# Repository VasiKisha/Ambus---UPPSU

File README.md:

# Ambus---UPPSU

View this project on [CADLAB.io](https://cadlab.io/project/24060). 

## Ambus Commands
|Command   |Description                          |
|:--------:|:-----------------------------------:|
| DEV?     | get device description              |
| FW?      | get firmware version                |
| SWITCH?  | get HW switch state                 |
| MODE?    | get CC/CV mode                      |
| VOLT?    | get measured output volrage         |
| CURR?    | get measured output current         |
| SETV(?)  | set(get) output voltage             |
| SETC(?)  | set(get) output current             |
| SWREM(?) | set(get) remote output control      |
| OUTPUT?  | get output relay state              |
| CALVG(?) | set(get) calibration voltage gain   |
| CALVO(?) | set(get) calibration voltage offset |
| CALIG(?) | set(get) calibration current gain   |
| CALIO(?) | set(get) calibration current offset |
| SAVE     | save settings to EEPROM             |
| LOAD     | load settings from EEPROM           |

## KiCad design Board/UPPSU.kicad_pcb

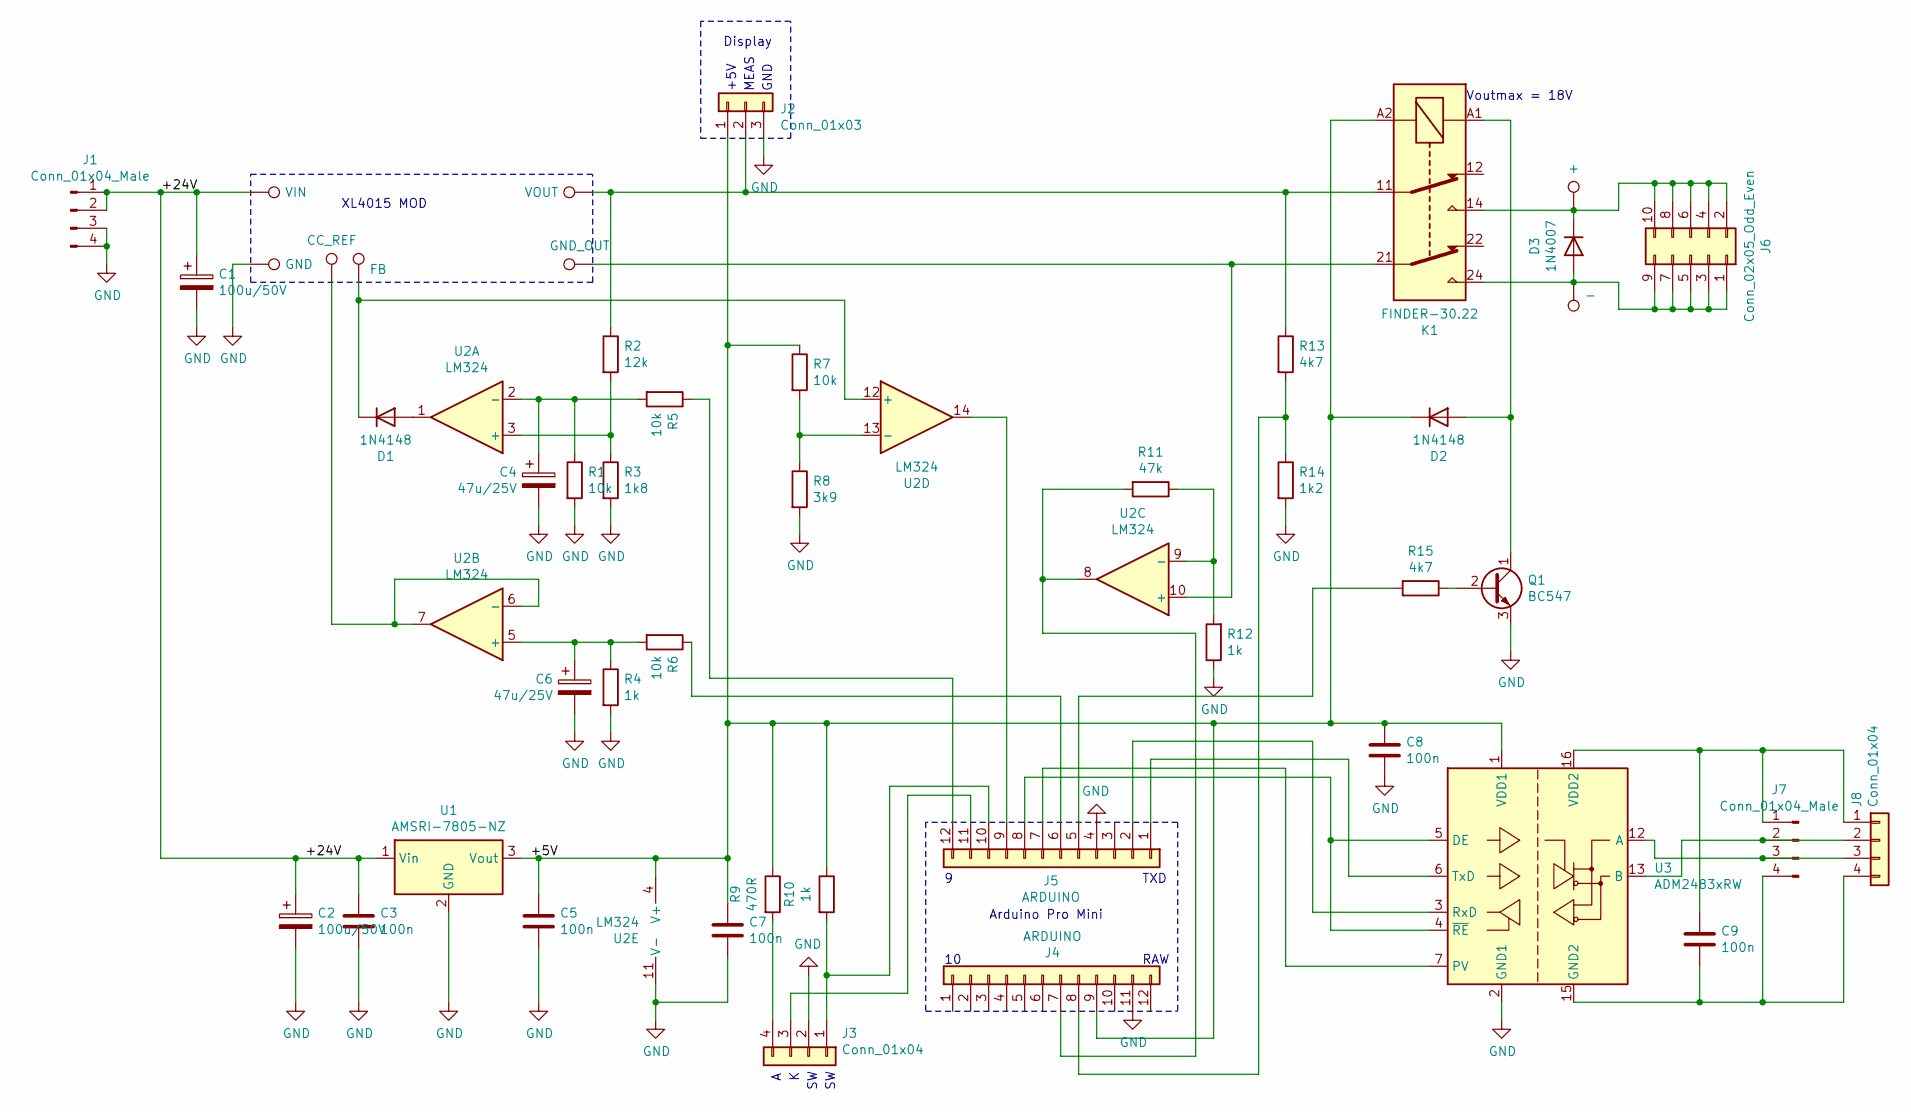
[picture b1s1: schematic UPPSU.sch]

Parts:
C1, C2: 100u/50V; CP_Radial_D16.0mm_P7.50mm
C3, C5, C7, C8, C9: 100n; C_Disc_D4.3mm_W1.9mm_P5.00mm
C4, C6: 47u/25V; CP_Radial_D5.0mm_P2.00mm
D1, D2: 1N4148; D_DO-35_SOD27_P7.62mm_Horizontal
D3: 1N4007; D_DO-35_SOD27_P7.62mm_Horizontal
J1, J7: Conn_01x04_Male; PhoenixContact_MSTBVA_2,5_4-G-5,08_1x04_P5.08mm_Vertical
J2: Conn_01x03; PinHeader_1x03_P2.54mm_Vertical
J3, J8: Conn_01x04; PinHeader_1x04_P2.54mm_Vertical
J4, J5: ARDUINO; PinSocket_1x12_P2.54mm_Vertical
J6: Conn_02x05_Odd_Even; PinSocket_2x05_P2.54mm_Horizontal
K1: FINDER-30.22; Relay_DPDT_Finder_30.22
Q1: BC547; TO-92_Inline
R1, R5, R6, R7: 10k; R_Axial_DIN0207_L6.3mm_D2.5mm_P7.62mm_Horizontal
R2: 12k; R_Axial_DIN0207_L6.3mm_D2.5mm_P7.62mm_Horizontal
R3: 1k8; R_Axial_DIN0207_L6.3mm_D2.5mm_P7.62mm_Horizontal
R4, R10, R12: 1k; R_Axial_DIN0207_L6.3mm_D2.5mm_P7.62mm_Horizontal
R8: 3k9; R_Axial_DIN0207_L6.3mm_D2.5mm_P7.62mm_Horizontal
R9: 470R; R_Axial_DIN0207_L6.3mm_D2.5mm_P7.62mm_Horizontal
R11: 47k; R_Axial_DIN0207_L6.3mm_D2.5mm_P7.62mm_Horizontal
R13, R15: 4k7; R_Axial_DIN0207_L6.3mm_D2.5mm_P7.62mm_Horizontal
R14: 1k2; R_Axial_DIN0207_L6.3mm_D2.5mm_P7.62mm_Horizontal
TP1: VIN; SolderWire-2.5sqmm_1x01_D2.4mm_OD4.4mm
TP2: GND; SolderWire-2.5sqmm_1x01_D2.4mm_OD4.4mm
TP3: CC_REF; SolderWire-0.25sqmm_1x01_D0.65mm_OD2mm
TP4: FB; SolderWire-0.25sqmm_1x01_D0.65mm_OD2mm
TP5: VOUT; SolderWire-2.5sqmm_1x01_D2.4mm_OD4.4mm
TP6: GND_OUT; SolderWire-2.5sqmm_1x01_D2.4mm_OD4.4mm
TP7: +; SolderWire-2.5sqmm_1x01_D2.4mm_OD4.4mm
TP8: -; SolderWire-2.5sqmm_1x01_D2.4mm_OD4.4mm
U1: AMSRI-7805-NZ; Converter_DCDC_TRACO_TSR-1_THT
U2: LM324; DIP-14_W7.62mm
U3: ADM2483xRW; SOIC-16W_7.5x10.3mm_P1.27mm

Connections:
/+5V: C5.1, C7.1, C8.1, D2.1 (K), J2.1, J4.9, K1.A2, R7.1, R9.1, R10.1, U1.3 (Vout), U2.4 (V+), U3.1 (VDD1)
/+24V: C1.1, C2.1, C3.1, J1.1, J1.2, TP1.1, U1.1 (Vin)
GND: C1.2, C2.2, C3.2, C4.2, C5.2, C6.2, C7.2, C8.2, J1.3, J1.4, J2.3, J3.2, J4.11, J5.4, Q1.3 (E), R1.2, R3.2, R4.2, R8.2, R12.1, R14.2, TP2.1, U1.2 (GND), U2.11 (V-), U3.2 (GND1), U3.8 (GND1)
unnamed: C4.1, R1.1, R5.2, U2.2 (-)
unnamed: C6.1, R4.1, R6.2, U2.5 (+)
unnamed: C9.1, J7.1, J8.1, U3.16 (VDD2)
unnamed: C9.2, J7.4, J8.4, U3.9 (GND2), U3.15 (GND2)
unnamed: D1.1 (K), TP4.1, U2.12 (+)
unnamed: D1.2 (A), U2.1
unnamed: D2.2 (A), K1.A1, Q1.1 (C)
unnamed: D3.1 (K), J6.2, J6.4, J6.6, J6.8, J6.10, K1.14, TP7.1
unnamed: D3.2 (A), J6.1, J6.3, J6.5, J6.7, J6.9, K1.24, TP8.1
unnamed: J2.2, K1.11, R2.1, R13.1, TP5.1
unnamed: J3.1, J5.10, R10.2
unnamed: J3.3, J5.11
unnamed: J3.4, R9.2
unnamed: J4.7, R11.2, U2.8
unnamed: J4.8, R13.2, R14.1
unnamed: J5.1, U3.6 (TxD)
unnamed: J5.2, U3.3 (RxD)
unnamed: J5.5, R15.2
unnamed: J5.6, R6.1
unnamed: J5.7, U3.7 (PV)
unnamed: J5.8, U3.4 (~RE), U3.5 (DE)
unnamed: J5.9, U2.14
unnamed: J5.12, R5.1
unnamed: J7.2, J8.2, U3.13 (B)
unnamed: J7.3, J8.3, U3.12 (A)
unnamed: K1.21, TP6.1, U2.10 (+)
unnamed: Q1.2 (B), R15.1
unnamed: R2.2, R3.1, U2.3 (+)
unnamed: R7.2, R8.1, U2.13 (-)
unnamed: R11.1, R12.2, U2.9 (-)
unnamed: TP3.1, U2.6 (-), U2.7

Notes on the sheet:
XL4015 MOD
Arduino Pro Mini
Display
Voutmax = 18V
RAW
TXD
+5V
MEAS
GND

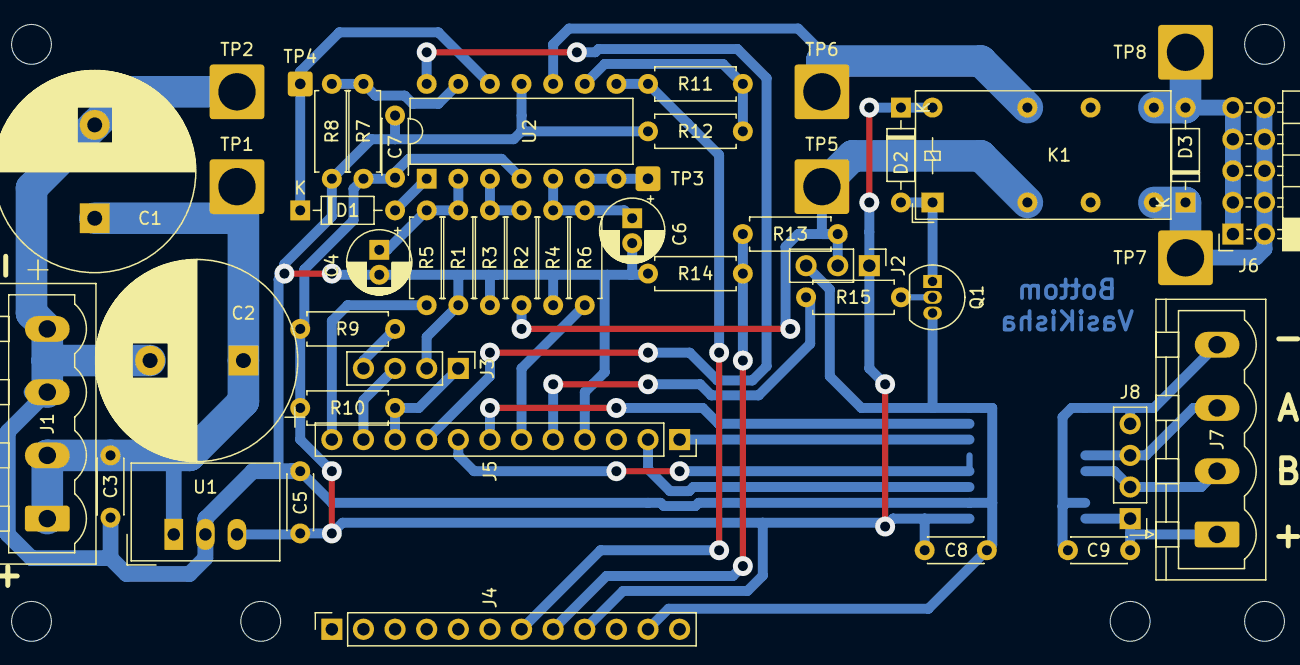
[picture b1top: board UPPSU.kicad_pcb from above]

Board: 2 copper layers, 48 parts (1 on the bottom side), 34 nets.

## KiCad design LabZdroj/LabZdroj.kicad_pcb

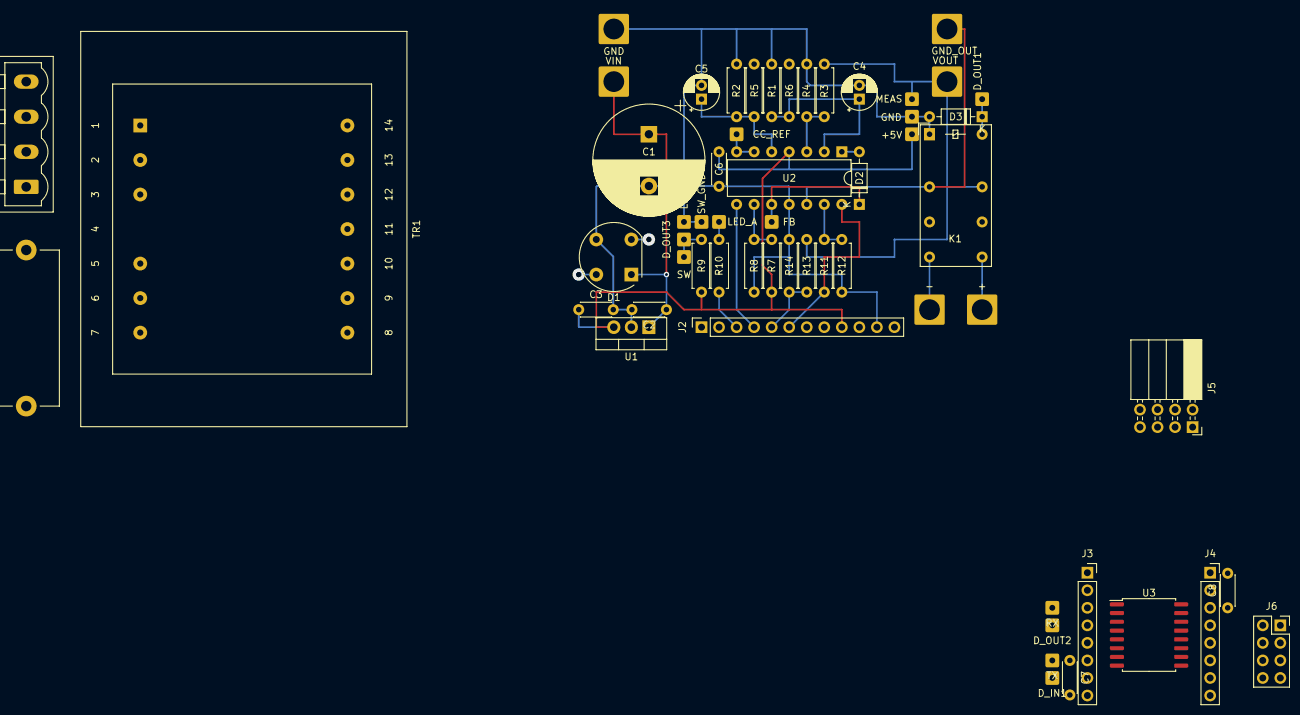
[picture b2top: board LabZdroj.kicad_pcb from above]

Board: 2 copper layers, 58 parts (0 on the bottom side), 37 nets.

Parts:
C1: 2200u/35V; CP_Radial_D16.0mm_P7.50mm
C2, C3, C6, C7, C8: 100n; C_Disc_D4.3mm_W1.9mm_P5.00mm
C4, C5: 47u/25V; CP_Radial_D5.0mm_P2.00mm
D1: W04G; Diode_Bridge_Round_D9.8mm
D2, D3: 1N4148; D_DO-35_SOD27_P7.62mm_Horizontal
F1: Fuse; Fuseholder_Cylinder-5x20mm_Stelvio-Kontek_PTF78_Horizontal_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
J1: Conn_01x04_Male; PhoenixContact_MSTBVA_2,5_4-G-5,08_1x04_P5.08mm_Vertical
J2: ARDUINO; PinSocket_1x12_P2.54mm_Vertical
J3, J4: ADM2483; PinSocket_1x08_P2.54mm_Vertical
J5: OUTPUT; PinSocket_2x04_P2.54mm_Horizontal
J6: COMM; PinSocket_2x04_P2.54mm_Vertical
K1: FINDER-30.22; Relay_DPDT_Finder_30.22
R1, R5, R6, R7: 10k; R_Axial_DIN0207_L6.3mm_D2.5mm_P7.62mm_Horizontal
R2, R9, R12: 1k; R_Axial_DIN0207_L6.3mm_D2.5mm_P7.62mm_Horizontal
R3: 12k; R_Axial_DIN0207_L6.3mm_D2.5mm_P7.62mm_Horizontal
R4: 1k8; R_Axial_DIN0207_L6.3mm_D2.5mm_P7.62mm_Horizontal
R8: 3k9; R_Axial_DIN0207_L6.3mm_D2.5mm_P7.62mm_Horizontal
R10: 470R; R_Axial_DIN0207_L6.3mm_D2.5mm_P7.62mm_Horizontal
R11: 47k; R_Axial_DIN0207_L6.3mm_D2.5mm_P7.62mm_Horizontal
R13: 4k7; R_Axial_DIN0207_L6.3mm_D2.5mm_P7.62mm_Horizontal
R14: 1k2; R_Axial_DIN0207_L6.3mm_D2.5mm_P7.62mm_Horizontal
TP1: VIN; SolderWire-2.5sqmm_1x01_D2.4mm_OD4.4mm
TP2: GND; SolderWire-2.5sqmm_1x01_D2.4mm_OD4.4mm
TP3: CC_REF; SolderWire-0.25sqmm_1x01_D0.65mm_OD2mm
TP4: FB; SolderWire-0.25sqmm_1x01_D0.65mm_OD2mm
TP5: VOUT; SolderWire-2.5sqmm_1x01_D2.4mm_OD4.4mm
TP6: GND_OUT; SolderWire-2.5sqmm_1x01_D2.4mm_OD4.4mm
TP7: +5V; SolderWire-0.25sqmm_1x01_D0.65mm_OD2mm
TP8: MEAS; SolderWire-0.25sqmm_1x01_D0.65mm_OD2mm
TP9: SW; SolderWire-0.25sqmm_1x01_D0.65mm_OD2mm
TP10: SW_GND; SolderWire-0.25sqmm_1x01_D0.65mm_OD2mm
TP11: GND; SolderWire-0.25sqmm_1x01_D0.65mm_OD2mm
TP12: LED_GND; SolderWire-0.25sqmm_1x01_D0.65mm_OD2mm
TP13: D_OUT3; SolderWire-0.25sqmm_1x01_D0.65mm_OD2mm
TP14: LED_A; SolderWire-0.25sqmm_1x01_D0.65mm_OD2mm
TP15: D_OUT1; SolderWire-0.25sqmm_1x01_D0.65mm_OD2mm
TP16: D_OUT2; SolderWire-0.25sqmm_1x01_D0.65mm_OD2mm
TP17: TX; SolderWire-0.25sqmm_1x01_D0.65mm_OD2mm
TP18: RX; SolderWire-0.25sqmm_1x01_D0.65mm_OD2mm
TP19: D_IN1; SolderWire-0.25sqmm_1x01_D0.65mm_OD2mm
TP20: +; SolderWire-2.5sqmm_1x01_D2.4mm_OD4.4mm
TP21: -; SolderWire-2.5sqmm_1x01_D2.4mm_OD4.4mm
TR1: TEZ16.0-D-18V; Transformer_Breve_TEZ-47x57
U1: LM7805_TO220; TO-220-3_Vertical
U2: LM324; DIP-14_W7.62mm
U3: ADM2483xRW; SOIC-16W_7.5x10.3mm_P1.27mm

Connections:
/+5V: C3.1, C6.1, C7.1, J2.9, J3.1, R7.1, R9.1, TP7.1, U1.3, U2.4, U3.1
/A_IN1: J2.6, R11.2, U2.14
/A_IN2: J2.5, R13.2, R14.1
/A_OUT1: J2.2, R6.1
/A_OUT2: J2.1, R5.1
/DIN_2: J2.4, U2.8
/D_OUT3: J2.3, R10.2
GND: C1.2, C2.2, C3.2, C4.2, C5.2, C6.2, C7.2, D1.3, D3.2, J2.11, J3.2, J3.8, K1.A1, R1.2, R2.2, R4.2, R8.2, R12.1, R14.2, TP2.1, TP10.1, TP11.1, TP12.1, U1.2, U2.11, U3.2, U3.8
unnamed: C1.1, C2.1, D1.1, TP1.1, U1.1
unnamed: C4.1, R1.1, R6.2, U2.2
unnamed: C5.1, R2.1, R5.2, U2.5
unnamed: C8.1, J4.8, J6.1, J6.2, U3.16
unnamed: C8.2, J4.1, J4.7, J6.7, J6.8, U3.9, U3.15
unnamed: D1.2, TR1.9
unnamed: D1.4, TR1.13
unnamed: D2.1, TP4.1, U2.10
unnamed: D2.2, U2.1
unnamed: D3.1, K1.A2, TP15.1
unnamed: F1.1, TR1.7
unnamed: F1.2, J1.1, J1.2
unnamed: J1.3, J1.4, TR1.1
unnamed: J3.3, TP18.1, U3.3
unnamed: J3.4, J3.5, TP16.1, U3.4, U3.5
unnamed: J3.6, TP17.1, U3.6
unnamed: J3.7, TP19.1, U3.7
unnamed: J4.4, J6.3, J6.4, U3.12
unnamed: J4.5, J6.5, J6.6, U3.13
unnamed: J5.1, J5.2, J5.3, J5.4, K1.24, TP20.1
unnamed: J5.5, J5.6, J5.7, J5.8, K1.14, TP21.1
unnamed: K1.11, TP6.1, U2.12
unnamed: K1.21, R3.1, R13.1, TP5.1, TP8.1
unnamed: R3.2, R4.1, U2.3
unnamed: R7.2, R8.1, U2.9
unnamed: R9.2, TP9.1, TP13.1
unnamed: R10.1, TP14.1
unnamed: R11.1, R12.2, U2.13
unnamed: TP3.1, U2.6, U2.7

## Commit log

2021-03-14 Initial release
2021-03-17 Ability to change/read address via broadcast, ack with device address, not MASTER
2021-03-18 Edited folder structure
2021-03-18 Edited project structure
2021-03-18 Backlink to CADLAB.io has been added.
2021-03-18 Create UPPSU.sch-bak
2021-03-18 TEST
2021-03-21 bord
2021-03-22 Board update
